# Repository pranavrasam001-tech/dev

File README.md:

# RP2040 PCB

## About the Project

This is a custom PCB designed in KiCad around the RP2040 microcontroller. The design includes USB Type-C connectivity, external flash memory, power regulation, a crystal oscillator, push-button control, and pin headers for external connections.

The project contains the complete schematic and PCB layout along with the Bill of Materials and Gerber manufacturing files.

---

## Features

- RP2040 microcontroller
- USB Type-C USB 2.0 interface
- W25Q128JVS external flash memory
- 3.3V voltage regulation
- External crystal oscillator
- Push button
- 20-pin header connectors
- 3-pin header connector
- SMD component design
- Two-layer PCB layout
- Gerber manufacturing files
- BOM exported as CSV

---

## Components Used

- RP2040
- W25Q128JVS
- MCP1700x-330xxTT
- USB Type-C Receptacle
- Crystal
- Push Button
- 1x20 Pin Headers
- 1x03 Pin Header
- Resistors
- Capacitors

---

##Images

---

## What I Did

- Created the schematic in KiCad.
- Added the RP2040 and supporting components.
- Added USB Type-C connectivity.
- Added external flash memory.
- Designed the power regulation section.
- Added the crystal oscillator circuit.
- Added required resistors and capacitors.
- Added push-button and header connections.
- Connected the required USB, power, ground, GPIO, QSPI, and clock signals.
- Created the PCB layout from the schematic.
- Assigned and placed component footprints.
- Routed the PCB connections.
- Prepared the PCB manufacturing layers.
- Generated the Gerber files.
- Generated the Bill of Materials.

---

## PCB Design

The PCB design uses front and back copper layers along with solder mask, silkscreen, paste, and edge-cut layers.

The design includes footprints for the RP2040, USB connector, external flash, regulator, crystal, headers, switch, resistors, and capacitors.

---

## What I Learned

- Creating schematics in KiCad
- Working with the RP2040
- USB Type-C connections
- External flash memory connections
- Power regulation design
- Component footprint selection
- PCB component placement
- PCB routing
- Working with multilayer PCB design files
- Generating a Bill of Materials
- Generating Gerber manufacturing files

---

## Project Files

```text
RP2040-PCB
│
├── Dev.kicad_pro
├── Dev.kicad_sch
├── Dev.kicad_pcb
├── Dev.csv
│
├── Gerber Files
│   ├── Dev-F_Cu.gbr
│   ├── Dev-B_Cu.gbr
│   ├── Dev-F_Mask.gbr
│   ├── Dev-B_Mask.gbr
│   ├── Dev-F_Silkscreen.gbr
│   ├── Dev-B_Silkscreen.gbr
│   ├── Dev-F_Paste.gbr
│   ├── Dev-B_Paste.gbr
│   ├── Dev-Edge_Cuts.gbr
│   └── Dev-job.gbrjob
│
└── README.md

GitHub: https://github.com/pranavrasam001-tech/dev.git

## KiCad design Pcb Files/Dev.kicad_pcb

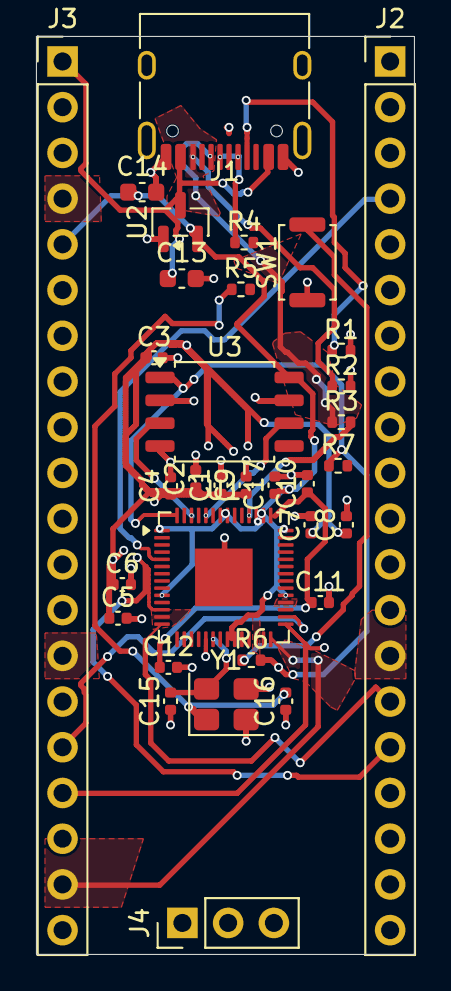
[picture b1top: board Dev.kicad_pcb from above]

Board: 2 copper layers, 21.0 x 51.0 mm, 33 parts (0 on the bottom side), 51 nets.

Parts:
C1, C10: 1uF; C_0402_1005Metric
C2, C3, C4, C5, C6, C7, C8, C9, C11, C12, C17: 0.1uF; C_0402_1005Metric
C13, C14: 10uF; C_0603_1608Metric
C15, C16: 33pF; C_0402_1005Metric
J1: USB_C_Receptacle_USB2.0_14P; USB_C_Receptacle_HRO_TYPE-C-31-M-12
J2, J3: Conn_01x20; PinHeader_1x20_P2.54mm_Vertical
J4: Conn_01x03; PinHeader_1x03_P2.54mm_Vertical
R1, R2: 5.1K; R_0402_1005Metric
R3, R4: 27; R_0402_1005Metric
R5, R6: 1K; R_0402_1005Metric
R7: 10K; R_0402_1005Metric
SW1: SW_Push; SW_Push_SPST_NO_Alps_SKRK
U1: RP2040; QFN-56-1EP_7x7mm_P0.4mm_EP3.2x3.2mm
U2: MCP1700x-330xxTT; SOT-23
U3: W25Q128JVS; SOIC-8_5.3x5.3mm_P1.27mm
Y1: Crystal_GND23_Small; Crystal_SMD_3225-4Pin_3.2x2.5mm

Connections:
+1V1: C10.1, C11.1, C12.1, U1.43 (ADC_AVDD), U1.48 (USB_VDD)
+3V3: C14.1, C17.1, J3.5, U1.1 (IOVDD), U1.10 (IOVDD), U1.22 (IOVDD), U1.23 (DVDD), U1.33 (IOVDD), U1.42 (IOVDD), U1.44 (VREG_VIN), U1.45 (VREG_VOUT), U1.49 (IOVDD), U1.50 (DVDD), U2.2 (VO), U3.8 (VCC)
/GPI026_ADC1: J3.7, U1.39 (GPIO27/ADC1)
/GPI026_ADC2: J3.4, U1.26 (RUN)
/GPI026_ADCO: J3.6, U1.40 (GPIO28/ADC2)
/GPIO0: J2.1, U1.7 (GPIO5)
/GPIO1: J2.2, U1.6 (GPIO4)
/GPIO2: J2.4, U1.5 (GPIO3)
/GPIO3: J2.5, U1.4 (GPIO2)
/GPIO4: J2.6, U1.3 (GPIO1)
/GPIO5: J2.7, U1.2 (GPIO0)
/GPIO6: J2.9, U1.18 (GPIO15)
/GPIO7: J2.10, U1.17 (GPIO14)
/GPIO8: J2.11, U1.16 (GPIO13)
/GPIO9: J2.12, U1.15 (GPIO12)
/GPIO10: J2.14, U1.13 (GPIO10)
/GPIO11: J2.15, U1.14 (GPIO11)
/GPIO12: J2.16, U1.12 (GPIO9)
/GPIO13: J2.17, U1.11 (GPIO8)
/GPIO14: J2.19, U1.9 (GPIO7)
/GPIO15: J2.20, U1.8 (GPIO6)
/GPIO16: J3.20, U1.27 (GPIO16)
/GPIO17: J3.19, U1.28 (GPIO17)
/GPIO18: J3.17, U1.29 (GPIO18)
/GPIO19: J3.16, U1.30 (GPIO19)
/GPIO20: J3.15, U1.31 (GPIO20)
/GPIO21: J3.14, U1.32 (GPIO21)
/GPIO22: J3.12, U1.34 (GPIO22)
/GPIO23: J3.10, U1.36 (GPIO24)
/GPIO24: J3.9, U1.38 (GPIO26/ADC0)
/QSPI_SCLK: U1.52 (QSPI_SCLK), U3.6 (CLK)
/QSPI_SD0: U1.53 (QSPI_SD0), U3.5 (DI/IO_{0})
/QSPI_SD1: U1.55 (QSPI_SD1), U3.2 (DO/IO_{1})
/QSPI_SD2: U1.54 (QSPI_SD2), U3.3 (~WP/IO_{2})
/QSPI_SD3: U1.51 (QSPI_SD3), U3.7 (~HOLD/~RESET/IO_{3})
/QSPI_SS: R6.2, R7.1, U1.56 (~QSPI_SS), U3.1 (~CS)
/RUN: J3.11, U1.35 (GPIO23)
/SWCLK: J4.1, U1.21 (XOUT)
/USB_D+: J1.A6 (D+), J1.B6 (D+), R2.1
/USB_D-: J1.A7 (D-), J1.B7 (D-), R4.1
/X_IN: C15.2, U1.20 (XIN), Y1.4
/X_OUT: R5.2, U1.24 (SWCLK)
GND: C1.2, C2.2, C3.2, C4.2, C5.2, C6.2, C7.2, C8.2, C9.2, C10.2, C11.2, C12.2, C13.2, C14.2, C15.1, C16.1, C17.2, J1.A1 (GND), J1.A12 (GND), J1.B1 (GND), J1.B12 (GND), J1.SH (SHIELD), J2.3, J2.8, J2.13, J2.18, J3.3, J3.8, J3.13, J3.18, J4.2, R1.2, R2.2, SW1.1, U1.19 (TESTEN), U1.57 (GND), U2.1 (GND), U3.4 (GND), Y1.2 (G), Y1.3 (G)
unnamed: C1.1, C2.1, C3.1, C4.1, C5.1, C6.1, C7.1, C8.1, C9.1
unnamed: C16.2, R5.1, Y1.1
unnamed: J1.A5 (CC1), R1.1
unnamed: J1.B5 (CC2), R3.1
unnamed: R6.1, SW1.2
unnamed: R3.2, U1.46 (USB_DM)
unnamed: R4.2, U1.47 (USB_DP)
VBUS: C13.1, J1.A4 (VBUS), J1.A9 (VBUS), J1.B4 (VBUS), J1.B9 (VBUS), J3.1, U2.3 (VI)

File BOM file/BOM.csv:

"Reference","Qty","Value","DNP","Exclude from BOM","Exclude from Board","Footprint","Datasheet"
"C1,C10","2","1uF","","","","Capacitor_SMD:C_0402_1005Metric",""
"C2,C3,C4,C5,C6,C7,C8,C9,C11,C12,C17","11","0.1uF","","","","Capacitor_SMD:C_0402_1005Metric",""
"C13,C14","2","10uF","","","","Capacitor_SMD:C_0603_1608Metric",""
"C15,C16","2","33pF","","","","Capacitor_SMD:C_0402_1005Metric",""
"J1","1","USB_C_Receptacle_USB2.0_14P","","","","Connector_USB:USB_C_Receptacle_HRO_TYPE-C-31-M-12","https://www.usb.org/sites/default/files/documents/usb_type-c.zip"
"J2,J3","2","Conn_01x20","","","","Connector_PinHeader_2.54mm:PinHeader_1x20_P2.54mm_Vertical",""
"J4","1","Conn_01x03","","","","Connector_PinHeader_2.54mm:PinHeader_1x03_P2.54mm_Vertical",""
"R1,R2","2","5.1K","","","","Resistor_SMD:R_0402_1005Metric",""
"R3,R4","2","27","","","","Resistor_SMD:R_0402_1005Metric",""
"R5,R6","2","1K","","","","Resistor_SMD:R_0402_1005Metric",""
"R7","1","10K","","","","Resistor_SMD:R_0402_1005Metric",""
"SW1","1","SW_Push","","","","Button_Switch_SMD:SW_Push_SPST_NO_Alps_SKRK",""
"U1","1","RP2040","","","","Package_DFN_QFN:QFN-56-1EP_7x7mm_P0.4mm_EP3.2x3.2mm","https://datasheets.raspberrypi.com/rp2040/rp2040-datasheet.pdf"
"U2","1","MCP1700x-330xxTT","","","","Package_TO_SOT_SMD:SOT-23","http://ww1.microchip.com/downloads/en/DeviceDoc/20001826D.pdf"
"U3","1","W25Q128JVS","","","","Package_SON:Winbond_USON-8-1EP_3x2mm_P0.5mm_EP0.2x1.6mm","https://www.winbond.com/resource-files/w25q128jv_dtr%20revc%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"
"Y1","1","Crystal_GND23_Small","","","","Crystal:Crystal_SMD_3225-4Pin_3.2x2.5mm",""
